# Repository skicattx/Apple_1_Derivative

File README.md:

# Apple_1_Derivative
Circuit Board based on various derivative designs of the original Apple I Hardware

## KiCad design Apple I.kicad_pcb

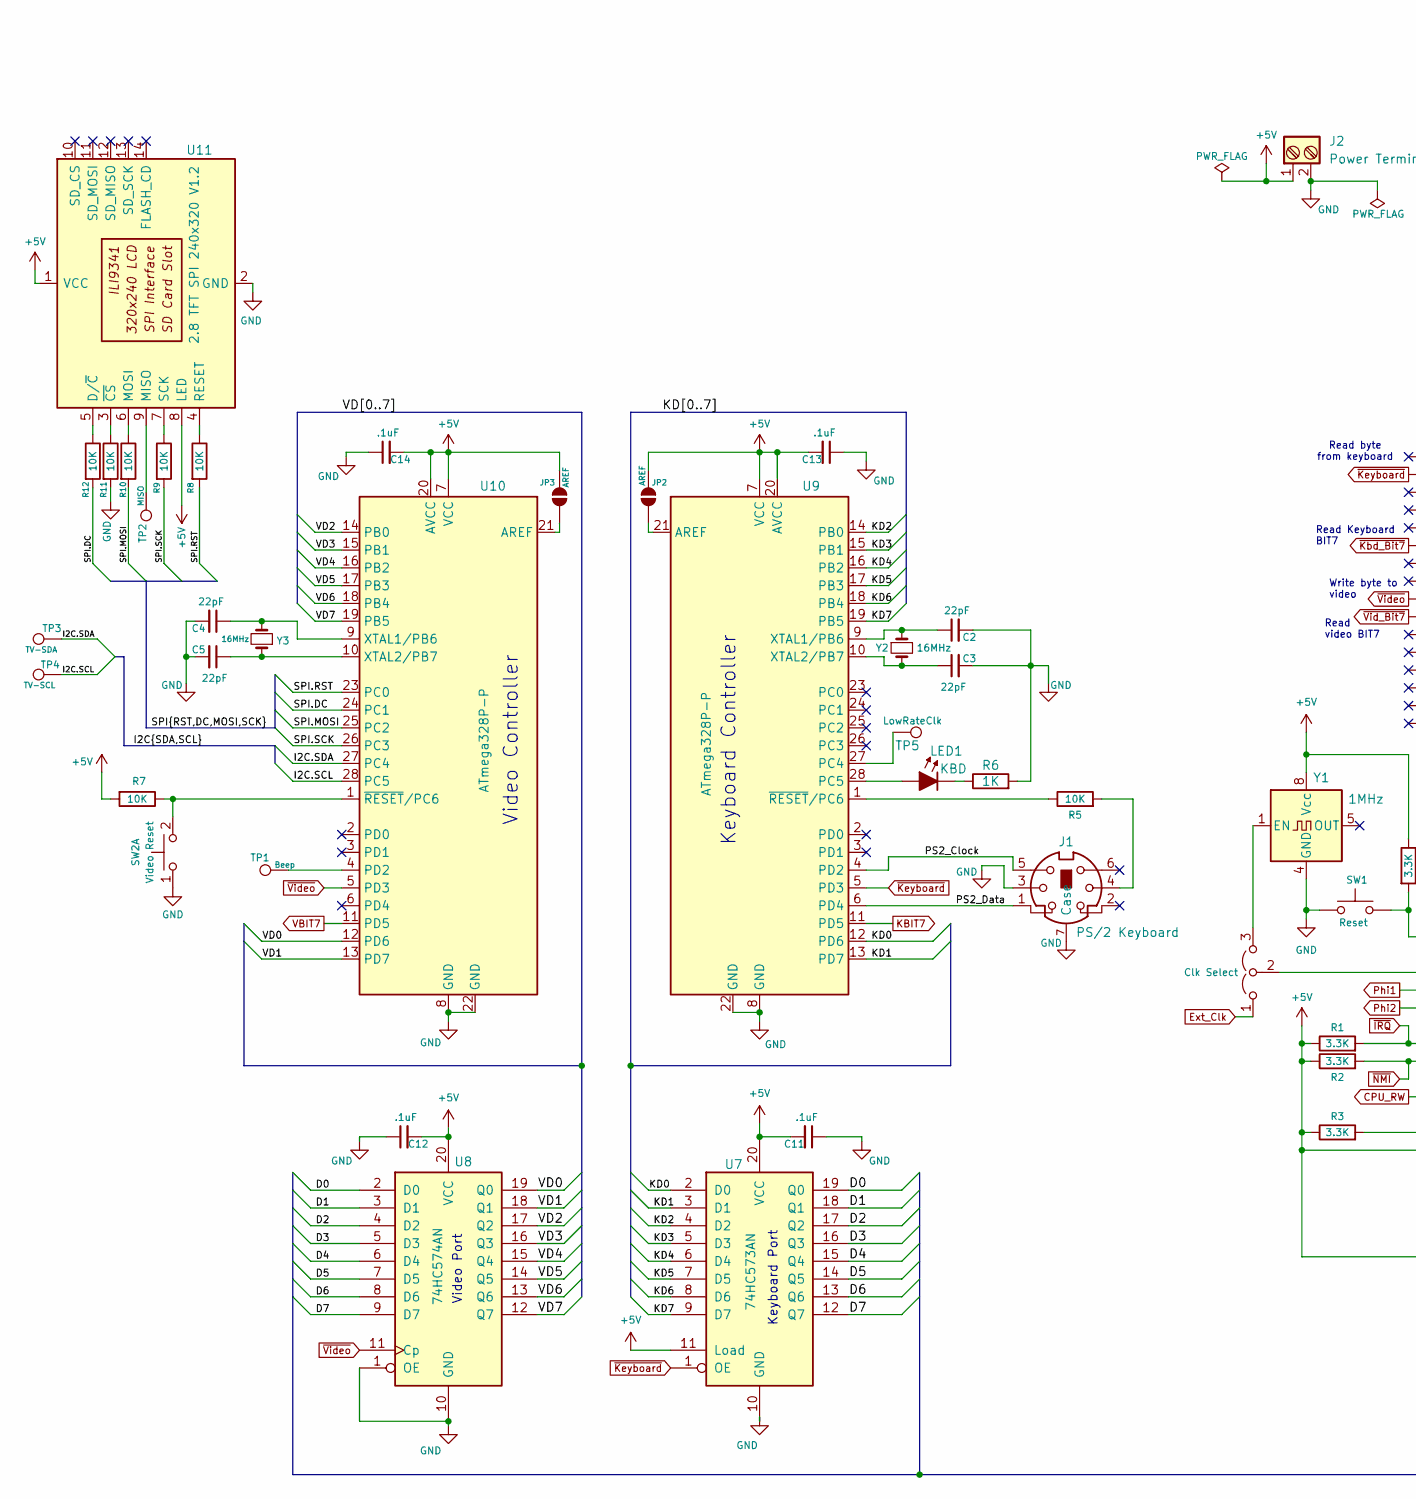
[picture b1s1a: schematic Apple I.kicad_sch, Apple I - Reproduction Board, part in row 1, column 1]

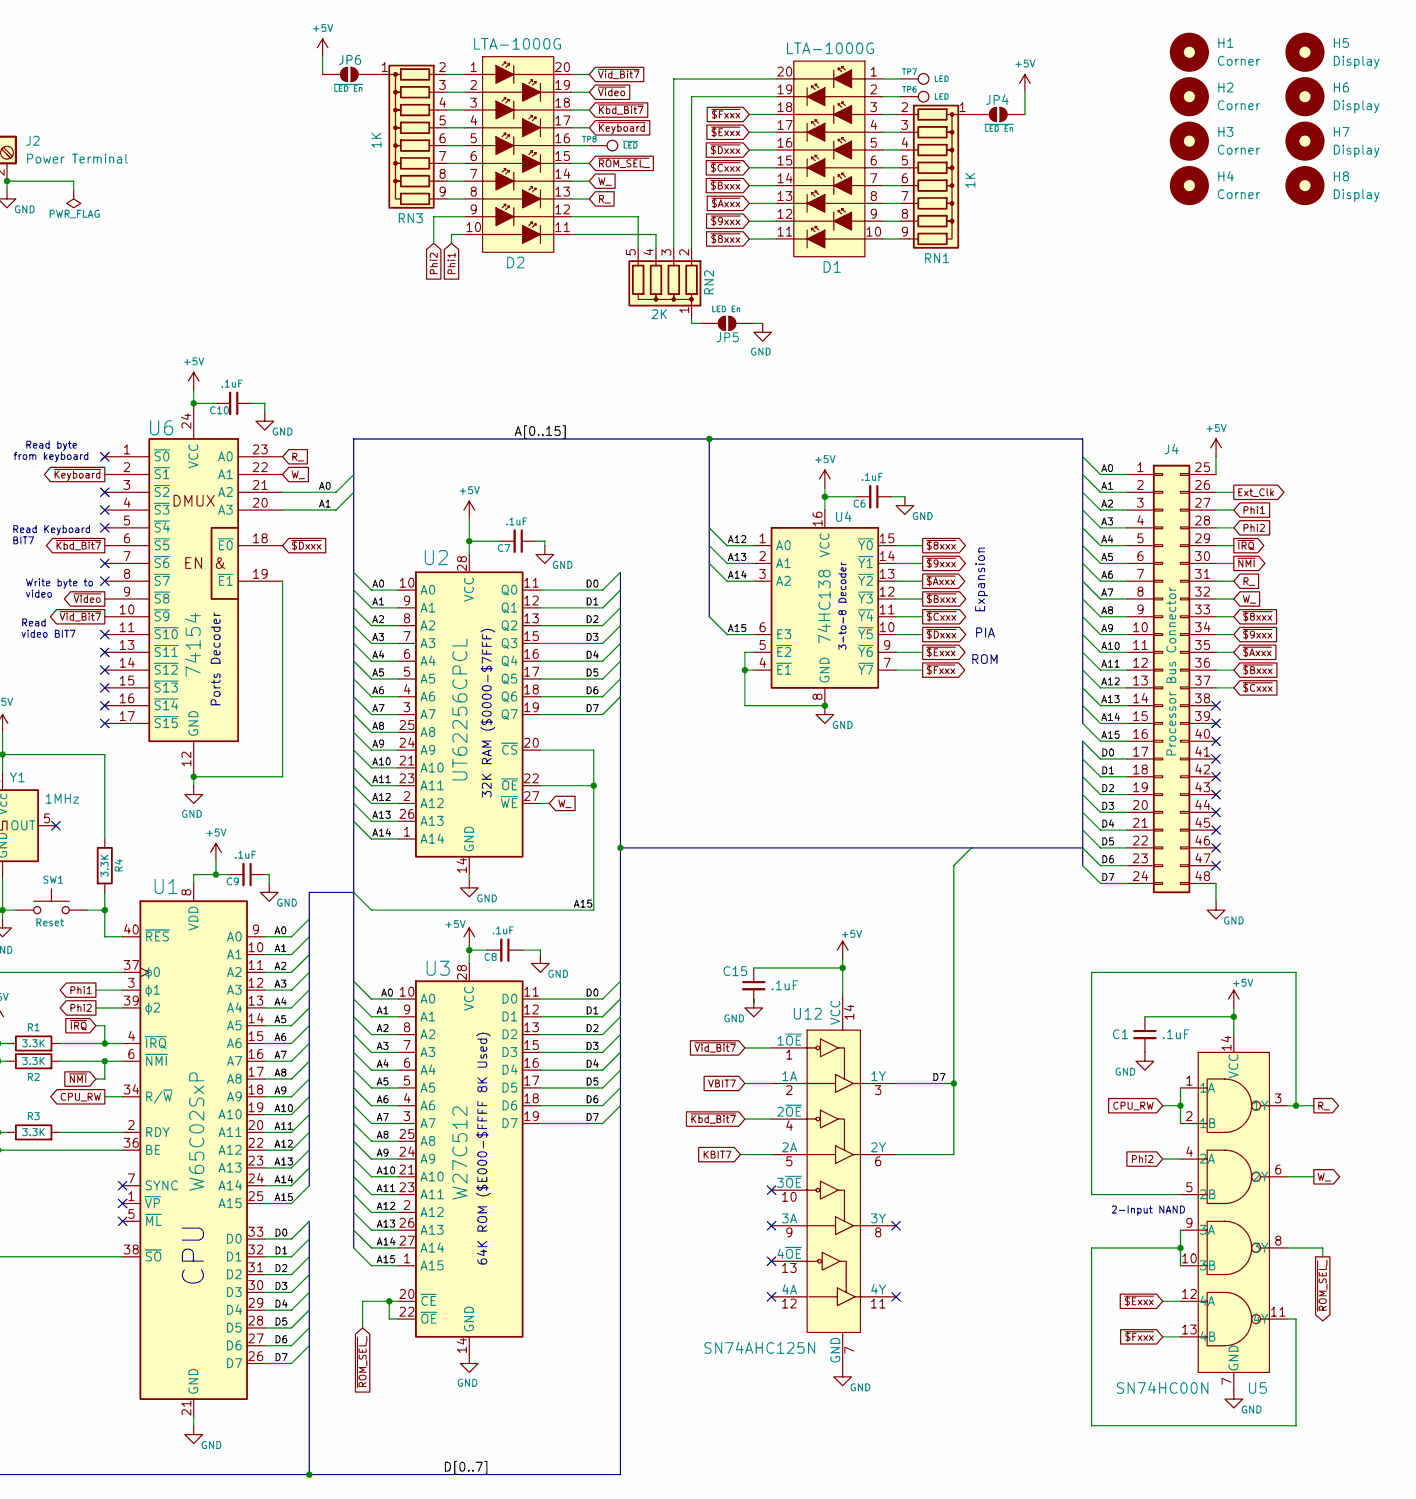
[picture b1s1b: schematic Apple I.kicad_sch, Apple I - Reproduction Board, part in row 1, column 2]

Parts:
C1, C6, C7, C8, C9, C10, C11, C12, C13, C14, C15: .1uF; C_Disc_D5.0mm_W2.5mm_P5.00mm
C2, C3, C4, C5: 22pF; C_Disc_D5.0mm_W2.5mm_P5.00mm
D1, D2: LTA-1000G; LED_Bar_Graph_LTA-1000; MPN LTA-1000G; Digi-Key_PN 160-1067-ND
H1, H2, H3, H4: Corner; MountingHole_3.2mm_M3
H5, H6, H7, H8: Display; MountingHole_3.2mm_M3
J1: PS/2 Keyboard; MINI-DIN-6-FULL-SHIELD
J2: Power Terminal; TerminalBlock_Phoenix_PT-1,5-2-5.0-H_1x02_P5.00mm_Horizontal
J4: Processor Bus Connector; PinHeader_2x24_P2.54mm_Vertical_Counter_Clockwise
JP1: Clk Select; PinHeader_1x03_P2.54mm_Vertical
JP2, JP3: AREF; SolderJumper-2_P1.3mm_Open_RoundedPad1.0x1.5mm
JP4, JP6: ~{LED En}; SolderJumper-2_P1.3mm_Open_RoundedPad1.0x1.5mm
JP5: LED En; SolderJumper-2_P1.3mm_Open_RoundedPad1.0x1.5mm
LED1: KBD; LED_D2.0mm_W4.8mm_H2.5mm_FlatTop
R1, R2, R3, R4: 3.3K; R_Axial_DIN0207_L6.3mm_D2.5mm_P10.16mm_Horizontal
R5, R7, R8, R9, R10, R11, R12: 10K; R_Axial_DIN0207_L6.3mm_D2.5mm_P10.16mm_Horizontal
R6: 1K; R_Axial_DIN0207_L6.3mm_D2.5mm_P10.16mm_Horizontal
RN1, RN3: 1K; R_Array_SIP9
RN2: 2K; R_Array_SIP5
SW1: Reset; Terminal_Block_D1.3mm_P5mm
SW2: Video Reset; Terminal_Block_D1.3mm_P5mm
TP1: Beep; TestPoint_THTPad_2.0x2.0mm_Drill1.0mm
TP2: MISO; TestPoint_THTPad_2.0x2.0mm_Drill1.0mm
TP3: TV-SDA; TestPoint_THTPad_2.0x2.0mm_Drill1.0mm
TP4: TV-SCL; TestPoint_THTPad_2.0x2.0mm_Drill1.0mm
TP5: LowRateClk; TestPoint_THTPad_2.0x2.0mm_Drill1.0mm
TP6, TP7: LED; TestPoint_THTPad_2.0x2.0mm_Drill1.0mm
TP8: ~{LED}; TestPoint_THTPad_2.0x2.0mm_Drill1.0mm
U1: W65C02SxP; DIP-40_W15.24mm_Socket
U2: UT62256CPCL; DIP-28_W15.24mm_Socket
U3: W27C512; DIP-28_W15.24mm_Socket
U4: 74HC138; DIP-16_W7.62mm_Socket
U5: SN74HC00N; DIP-14_W7.62mm_Socket; MPN SN74HC00N; Digi-Key_PN 296-1563-5-ND
U6: 74154; DIP-24_W7.62mm_Socket
U7: 74HC573AN; DIP-20_W7.62mm_Socket
U8: 74HC574AN; DIP-20_W7.62mm_Socket
U9, U10: ATmega328P-P; DIP-28_W7.62mm_Socket
U11: 2.8 TFT SPI 240x320 V1.2; TFT-320x240
U12: SN74AHC125N; DIP-14_W7.62mm_Socket; MPN SN74AHCT125N; Digi-Key_PN 296-4655-5-ND
Y1: 1MHz; Oscillator_DIP-8
Y2, Y3: 16MHz; Crystal_HC49-4H_Vertical

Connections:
+5V: C1.1, C6.2, C7.2, C8.2, C9.2, C10.2, C11.2, C12.2, C13.2, C14.2, C15.1, J2.1, J4.25, JP2.2 (B), JP3.2 (B), JP4.2 (B), JP6.2 (B), R1.1, R2.1, R3.1, R4.1, R7.2, U1.8 (VDD), U1.36 (BE), U1.38 (~SO), U2.28 (VCC), U3.28 (VCC), U4.16 (VCC), U5.14 (VCC), U6.24 (VCC), U7.11 (Load), U7.20 (VCC), U8.20 (VCC), U9.7 (VCC), U9.20 (AVCC), U10.7 (VCC), U10.20 (AVCC), U11.1 (VCC), U11.8 (LED), U12.14 (VCC), Y1.8 (Vcc)
/A0: J4.1, U1.9 (A0), U2.10 (A0), U3.10 (A0), U6.21 (A2)
/A1: J4.2, U1.10 (A1), U2.9 (A1), U3.9 (A1), U6.20 (A3)
/A2: J4.3, U1.11 (A2), U2.8 (A2), U3.8 (A2)
/A3: J4.4, U1.12 (A3), U2.7 (A3), U3.7 (A3)
/A4: J4.5, U1.13 (A4), U2.6 (A4), U3.6 (A4)
/A5: J4.6, U1.14 (A5), U2.5 (A5), U3.5 (A5)
/A6: J4.7, U1.15 (A6), U2.4 (A6), U3.4 (A6)
/A7: J4.8, U1.16 (A7), U2.3 (A7), U3.3 (A7)
/A8: J4.9, U1.17 (A8), U2.25 (A8), U3.25 (A8)
/A9: J4.10, U1.18 (A9), U2.24 (A9), U3.24 (A9)
/A10: J4.11, U1.19 (A10), U2.21 (A10), U3.21 (A10)
/A11: J4.12, U1.20 (A11), U2.23 (A11), U3.23 (A11)
/A12: J4.13, U1.22 (A12), U2.2 (A12), U3.2 (A12), U4.1 (A0)
/A13: J4.14, U1.23 (A13), U2.26 (A13), U3.26 (A13), U4.2 (A1)
/A14: J4.15, U1.24 (A14), U2.1 (A14), U3.27 (A14), U4.3 (A2)
/A15: J4.16, U1.25 (A15), U2.20 (~CS), U2.22 (~OE), U3.1 (A15), U4.6 (E3)
/D0: J4.17, U1.33 (D0), U2.11 (Q0), U3.11 (D0), U7.19 (Q0), U8.2 (D0)
/D1: J4.18, U1.32 (D1), U2.12 (Q1), U3.12 (D1), U7.18 (Q1), U8.3 (D1)
/D2: J4.19, U1.31 (D2), U2.13 (Q2), U3.13 (D2), U7.17 (Q2), U8.4 (D2)
/D3: J4.20, U1.30 (D3), U2.15 (Q3), U3.15 (D3), U7.16 (Q3), U8.5 (D3)
/D4: J4.21, U1.29 (D4), U2.16 (Q4), U3.16 (D4), U7.15 (Q4), U8.6 (D4)
/D5: J4.22, U1.28 (D5), U2.17 (Q5), U3.17 (D5), U7.14 (Q5), U8.7 (D5)
/D6: J4.23, U1.27 (D6), U2.18 (Q6), U3.18 (D6), U7.13 (Q6), U8.8 (D6)
/D7: J4.24, U1.26 (D7), U2.19 (Q7), U3.19 (D7), U7.12 (Q7), U8.9 (D7), U12.3 (1Y), U12.6 (2Y)
/I2C.SCL: TP4.1, U10.28 (PC5)
/I2C.SDA: TP3.1, U10.27 (PC4)
/KD0: U7.2 (D0), U9.12 (PD6)
/KD1: U7.3 (D1), U9.13 (PD7)
/KD2: U7.4 (D2), U9.14 (PB0)
/KD3: U7.5 (D3), U9.15 (PB1)
/KD4: U7.6 (D4), U9.16 (PB2)
/KD5: U7.7 (D5), U9.17 (PB3)
/KD6: U7.8 (D6), U9.18 (PB4)
/KD7: U7.9 (D7), U9.19 (PB5)
/PS2_Clock: J1.5, U9.4 (PD2)
/PS2_Data: J1.1, U9.6 (PD4)
/SPI.DC: R12.2, U10.24 (PC1)
/SPI.MOSI: R10.2, U10.25 (PC2)
/SPI.RST: R8.2, U10.23 (PC0)
/SPI.SCK: R9.2, U10.26 (PC3)
/VD0: U8.19 (Q0), U10.12 (PD6)
/VD1: U8.18 (Q1), U10.13 (PD7)
/VD2: U8.17 (Q2), U10.14 (PB0)
/VD3: U8.16 (Q3), U10.15 (PB1)
/VD4: U8.15 (Q4), U10.16 (PB2)
/VD5: U8.14 (Q5), U10.17 (PB3)
/VD6: U8.13 (Q6), U10.18 (PB4)
/VD7: U8.12 (Q7), U10.19 (PB5)
CPU_RW: U1.34 (R/~W), U5.1 (1A), U5.2 (1B)
Ext_Clk: J4.26, JP1.1 (A)
GND: C1.2, C2.2, C3.2, C4.2, C5.2, C6.1, C7.1, C8.1, C9.1, C10.1, C11.1, C12.1, C13.1, C14.1, C15.2, J1.3, J1.7 (Case), J2.2, J4.48, JP5.1 (A), R6.2, R11.2, SW1.1, SW2.1 (C), U1.21 (GND), U2.14 (GND), U3.14 (GND), U4.4 (~E1), U4.5 (~E2), U4.8 (GND), U5.7 (GND), U6.12 (GND), U6.19 (~E1), U7.10 (GND), U8.1 (OE), U8.10 (GND), U9.8 (GND), U9.22 (GND), U10.8 (GND), U10.22 (GND), U11.2 (GND), U12.7 (GND), Y1.4 (GND)
KBIT7: U9.11 (PD5), U12.5 (2A)
unnamed: D1.1, TP7.1
unnamed: D1.2, TP6.1
unnamed: D2.16, TP8.1
unnamed: J1.4, R5.2
unnamed: JP1.3 (B), Y1.1 (EN)
unnamed: JP1.2 (C), U1.37 (ϕ0)
unnamed: JP2.1 (A), U9.21 (AREF)
unnamed: JP3.1 (A), U10.21 (AREF)
unnamed: JP4.1 (A), RN1.1 (common)
unnamed: JP5.2 (B), RN2.1 (common)
unnamed: JP6.1 (A), RN3.1 (common)
unnamed: LED1.2 (A), U9.28 (PC5)
unnamed: LED1.1 (K), R6.1
unnamed: D1.3, RN1.2 (R1)
unnamed: D1.4, RN1.3 (R2)
unnamed: D1.5, RN1.4 (R3)
unnamed: D1.6, RN1.5 (R4)
unnamed: D1.7, RN1.6 (R5)
unnamed: D1.8, RN1.7 (R6)
unnamed: D1.9, RN1.8 (R7)
unnamed: D1.10, RN1.9 (R8)
unnamed: D1.19, RN2.2 (R1)
unnamed: D1.20, RN2.3 (R2)
unnamed: D2.11, RN2.4 (R3)
unnamed: D2.12, RN2.5 (R4)
unnamed: D2.1, RN3.2 (R1)
unnamed: D2.2, RN3.3 (R2)
unnamed: D2.3, RN3.4 (R3)
unnamed: D2.4, RN3.5 (R4)
unnamed: D2.5, RN3.6 (R5)
unnamed: D2.6, RN3.7 (R6)
unnamed: D2.7, RN3.8 (R7)
unnamed: D2.8, RN3.9 (R8)
unnamed: R7.1, SW2.2 (D), U10.1 (~RESET/PC6)
unnamed: R3.2, U1.2 (RDY)
unnamed: R4.2, SW1.2, U1.40 (~RES)
unnamed: U5.9 (3A), U5.10 (3B), U5.11 (4Y)
unnamed: TP5.1, U9.27 (PC4)
unnamed: C2.1, U9.9 (XTAL1/PB6), Y2.1
unnamed: C3.1, U9.10 (XTAL2/PB7), Y2.2
unnamed: R5.1, U9.1 (~RESET/PC6)
unnamed: TP1.1, U10.4 (PD2)
unnamed: C4.1, U10.9 (XTAL1/PB6), Y3.2
unnamed: C5.1, U10.10 (XTAL2/PB7), Y3.1
unnamed: R12.1, U11.5 (D/~C)
unnamed: TP2.1, U11.9 (MISO)
unnamed: R10.1, U11.6 (MOSI)
unnamed: R8.1, U11.4 (RESET)
unnamed: R9.1, U11.7 (SCK)
unnamed: R11.1, U11.3 (~CS)
Phi1: D2.10, J4.27, U1.3 (ϕ1)
Phi2: D2.9, J4.28, U1.39 (ϕ2), U5.4 (2A)
R_: D2.13, J4.31, U5.3 (1Y), U5.5 (2B), U6.23 (A0)
VBIT7: U10.11 (PD5), U12.2 (1A)
W_: D2.14, J4.32, U2.27 (~WE), U5.6 (2Y), U6.22 (A1)
~$8xxx: D1.11, J4.33, U4.15 (~Y0)
~$9xxx: D1.12, J4.34, U4.14 (~Y1)
~$Axxx: D1.13, J4.35, U4.13 (~Y2)
~$Bxxx: D1.14, J4.36, U4.12 (~Y3)
~$Cxxx: D1.15, J4.37, U4.11 (~Y4)
~$Dxxx: D1.16, U4.10 (~Y5), U6.18 (~E0)
~$Exxx: D1.17, U4.9 (~Y6), U5.12 (4A)
~$Fxxx: D1.18, U4.7 (~Y7), U5.13 (4B)
~IRQ: J4.29, R1.2, U1.4 (~IRQ)
~Kbd_Bit7: D2.18, U6.6 (~S5), U12.4 (2~OE)
~Keyboard: D2.17, U6.2 (~S1), U7.1 (OE), U9.5 (PD3)
~NMI: J4.30, R2.2, U1.6 (~NMI)
~ROM_SEL_: D2.15, U3.20 (~CE), U3.22 (~OE), U5.8 (3Y)
~Vid_Bit7: D2.20, U6.10 (~S9), U12.1 (1~OE)
~Video: D2.19, U6.9 (~S8), U8.11 (Cp), U10.5 (PD3)

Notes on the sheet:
ROM
PIA
Read video BIT7
Write byte to video
Keyboard Controller
2-Input NAND
32K RAM ($0000-$7FFF)
Ports Decoder
3-to-8 Decoder
Keyboard Port
64K ROM ($E000-$FFFF 8K Used)
CPU
Expansion
Read Keyboard BIT7
Video Controller
Read byte from keyboard
Video Port

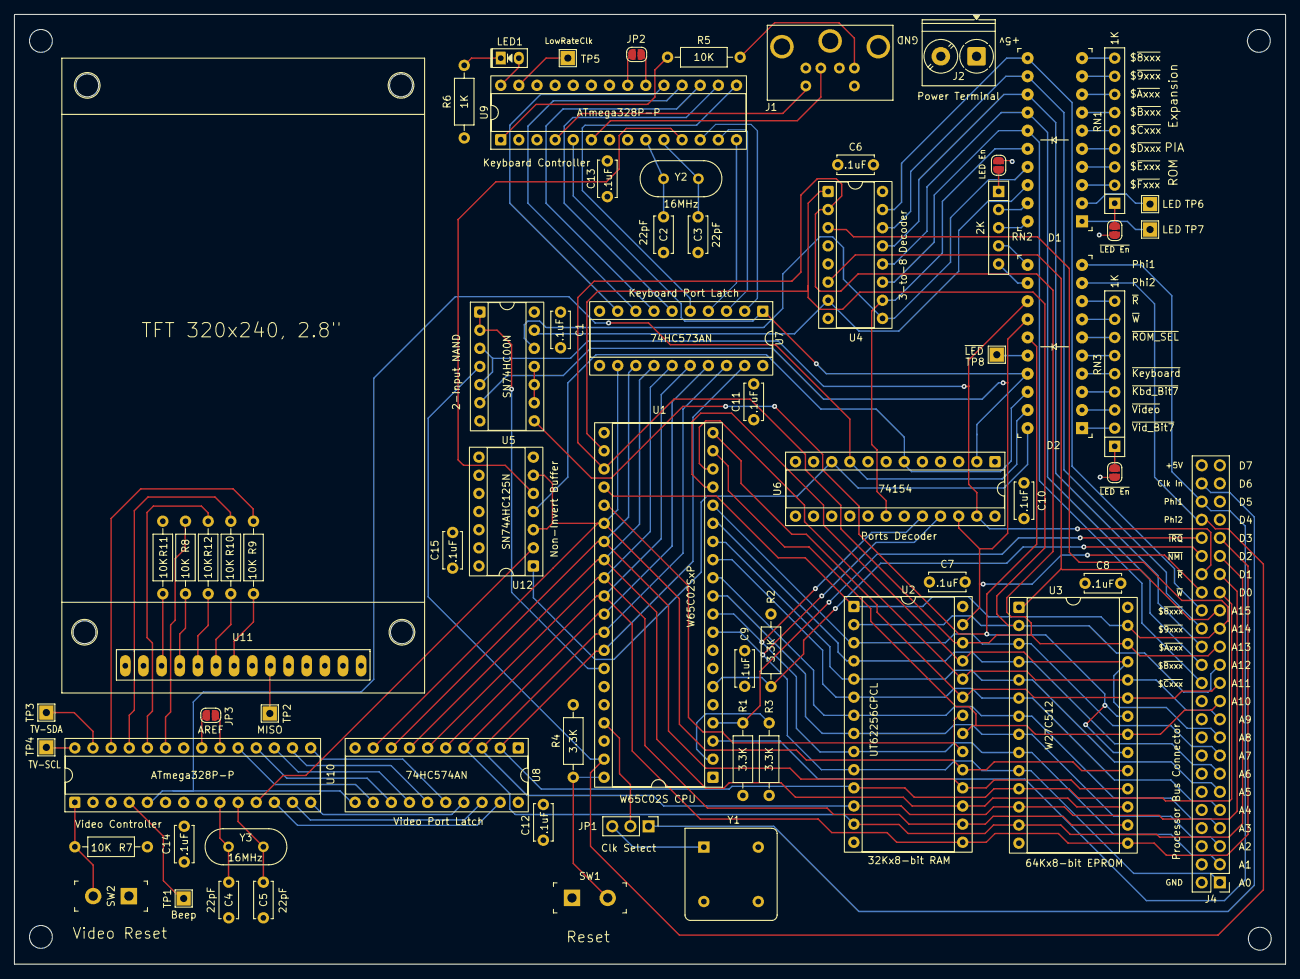
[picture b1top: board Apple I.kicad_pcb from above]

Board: 4 copper layers, 178.0 x 133.0 mm, 75 parts (0 on the bottom side), 123 nets.

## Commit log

2025-02-23 Initial Kicad 8 files
2025-02-23 add ignore file
2025-02-23 add ds store
2025-02-23 Update to 9
2025-02-28 Working on Video and Keyboard controllers
2025-03-04 Schematic 1.0 add footprints and pcb
2025-03-05 Additional pcb layout
2025-03-07 More work on PCB Placement and routing
2025-03-17 First pass routing finished

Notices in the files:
Apple I.kicad_pcb:
https://creativecommons.org/licenses/by-nc-sa/4.0
This work is licensed under CC BY-NC-SA 4.0
